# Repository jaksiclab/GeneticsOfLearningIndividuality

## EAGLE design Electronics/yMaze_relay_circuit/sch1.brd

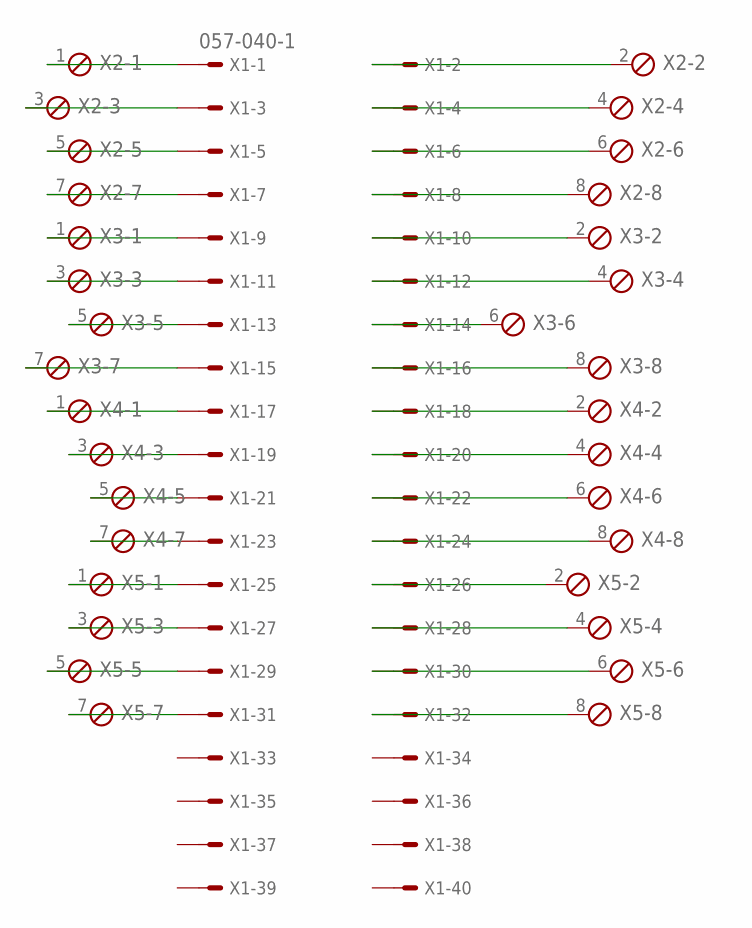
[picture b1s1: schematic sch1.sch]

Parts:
X1: 057-040-1
X2, X3, X4, X5: MPT8; 8POL254

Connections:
unnamed: X1.1, X2.1
unnamed: X1.2, X2.2
unnamed: X1.3, X2.3
unnamed: X1.4, X2.4
unnamed: X1.5, X2.5
unnamed: X1.6, X2.6
unnamed: X1.7, X2.7
unnamed: X1.8, X2.8
unnamed: X1.9, X3.1
unnamed: X1.10, X3.2
unnamed: X1.11, X3.3
unnamed: X1.12, X3.4
unnamed: X1.13, X3.5
unnamed: X1.14, X3.6
unnamed: X1.15, X3.7
unnamed: X1.16, X3.8
unnamed: X1.17, X4.1
unnamed: X1.18, X4.2
unnamed: X1.19, X4.3
unnamed: X1.20, X4.4
unnamed: X1.21, X4.5
unnamed: X1.22, X4.6
unnamed: X1.23, X4.7
unnamed: X1.24, X4.8
unnamed: X1.25, X5.1
unnamed: X1.26, X5.2
unnamed: X1.27, X5.3
unnamed: X1.28, X5.4
unnamed: X1.29, X5.5
unnamed: X1.30, X5.6
unnamed: X1.31, X5.7
unnamed: X1.32, X5.8

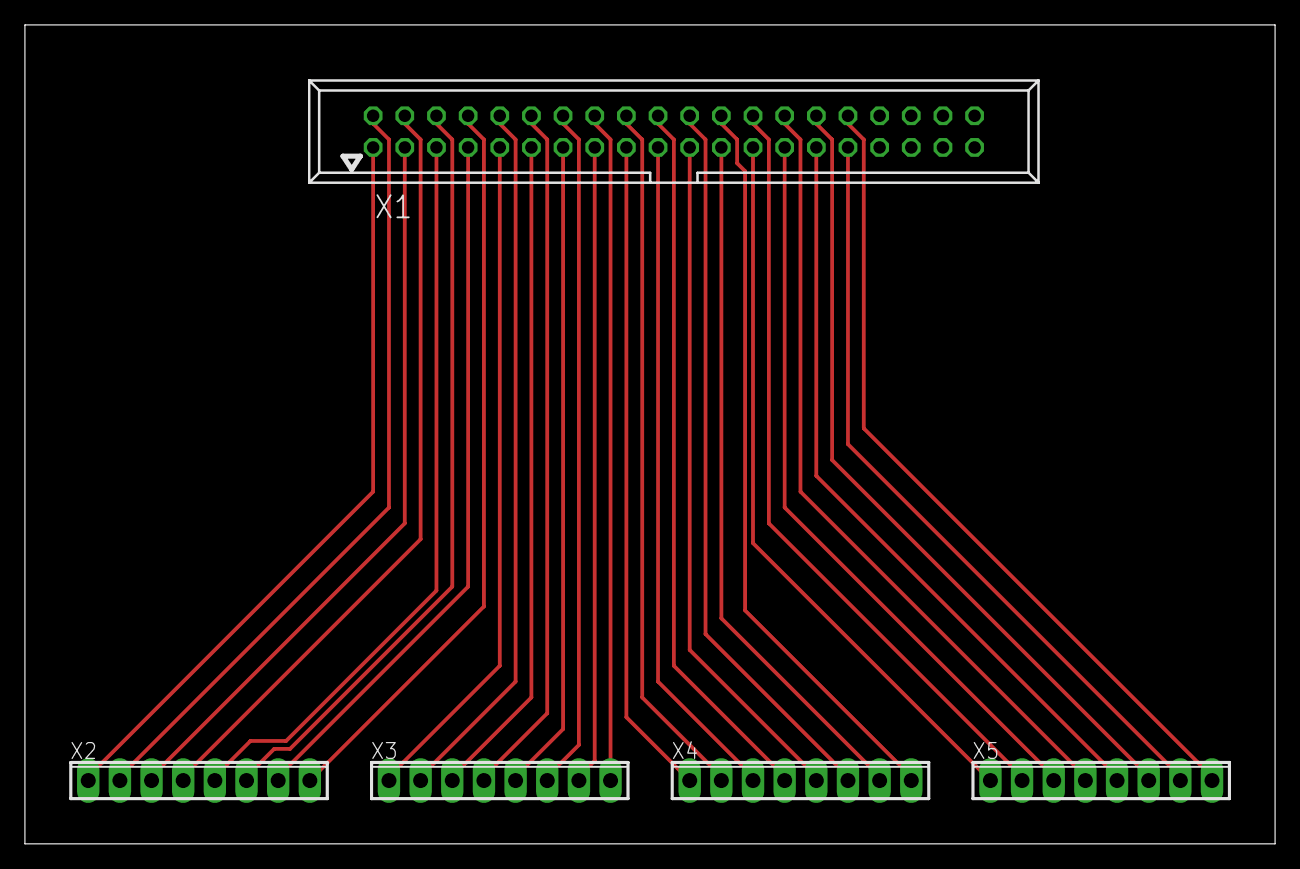
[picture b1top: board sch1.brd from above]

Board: 2 copper layers, 100.3 x 65.7 mm, 5 parts (0 on the bottom side), 32 nets.

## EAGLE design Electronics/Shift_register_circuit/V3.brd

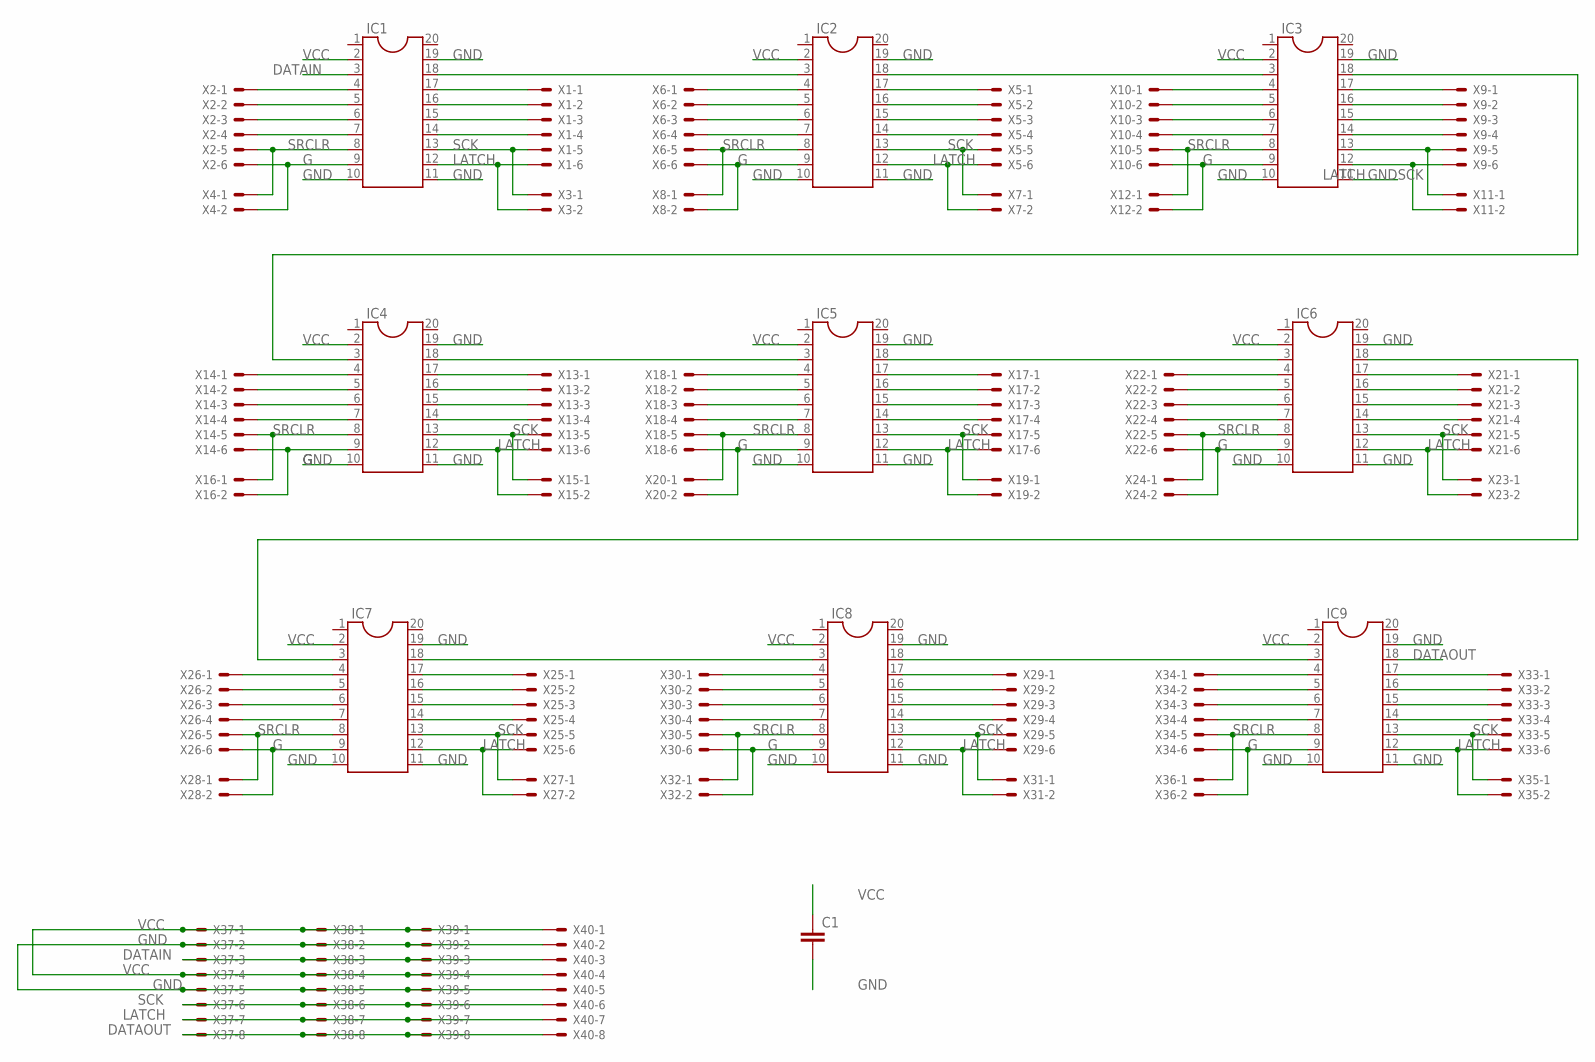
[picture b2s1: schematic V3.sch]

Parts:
C1: C2.5/2; C2.5-2
IC1, IC2, IC3, IC4, IC5, IC6, IC7, IC8, IC9: DIL20
X1, X2, X5, X6, X9, X10, X13, X14, X17, X18, X21, X22, X25, X26, X29, X30, X33, X34: 22-23-2061
X3, X4, X7, X8, X11, X12, X15, X16, X19, X20, X23, X24, X27, X28, X31, X32, X35, X36: 22-23-2021
X37, X38, X39, X40: 22-23-2081

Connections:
DATAIN: IC1.3, X37.3, X38.3, X39.3, X40.3
DATAOUT: IC9.18, X37.8, X38.8, X39.8, X40.8
G: IC1.9, IC2.9, IC3.9, IC4.9, IC5.9, IC6.9, IC7.9, IC8.9, IC9.9, X2.6, X4.2, X6.6, X8.2, X10.6, X12.2, X14.6, X16.2, X18.6, X20.2, X22.6, X24.2, X26.6, X28.2, X30.6, X32.2, X34.6, X36.2
GND: C1.2, IC1.10, IC1.11, IC1.19, IC2.10, IC2.11, IC2.19, IC3.10, IC3.11, IC3.19, IC4.10, IC4.11, IC4.19, IC5.10, IC5.11, IC5.19, IC6.10, IC6.11, IC6.19, IC7.10, IC7.11, IC7.19, IC8.10, IC8.11, IC8.19, IC9.10, IC9.11, IC9.19, X37.2, X37.5, X38.2, X38.5, X39.2, X39.5, X40.2, X40.5
LATCH: IC1.12, IC2.12, IC3.12, IC4.12, IC5.12, IC6.12, IC7.12, IC8.12, IC9.12, X1.6, X3.2, X5.6, X7.2, X9.6, X11.2, X13.6, X15.2, X17.6, X19.2, X21.6, X23.2, X25.6, X27.2, X29.6, X31.2, X33.6, X35.2, X37.7, X38.7, X39.7, X40.7
unnamed: IC1.17, X1.1
unnamed: IC1.16, X1.2
unnamed: IC1.15, X1.3
unnamed: IC1.14, X1.4
unnamed: IC1.4, X2.1
unnamed: IC1.5, X2.2
unnamed: IC1.6, X2.3
unnamed: IC1.7, X2.4
unnamed: IC2.17, X5.1
unnamed: IC2.16, X5.2
unnamed: IC2.15, X5.3
unnamed: IC2.14, X5.4
unnamed: IC2.4, X6.1
unnamed: IC2.5, X6.2
unnamed: IC2.6, X6.3
unnamed: IC2.7, X6.4
unnamed: IC3.17, X9.1
unnamed: IC3.16, X9.2
unnamed: IC3.15, X9.3
unnamed: IC3.14, X9.4
unnamed: IC3.4, X10.1
unnamed: IC3.5, X10.2
unnamed: IC3.6, X10.3
unnamed: IC3.7, X10.4
unnamed: IC4.17, X13.1
unnamed: IC4.16, X13.2
unnamed: IC4.15, X13.3
unnamed: IC4.14, X13.4
unnamed: IC4.4, X14.1
unnamed: IC4.5, X14.2
unnamed: IC4.6, X14.3
unnamed: IC4.7, X14.4
unnamed: IC5.17, X17.1
unnamed: IC5.16, X17.2
unnamed: IC5.15, X17.3
unnamed: IC5.14, X17.4
unnamed: IC5.4, X18.1
unnamed: IC5.5, X18.2
unnamed: IC5.6, X18.3
unnamed: IC5.7, X18.4
unnamed: IC6.17, X21.1
unnamed: IC6.16, X21.2
unnamed: IC6.15, X21.3
unnamed: IC6.14, X21.4
unnamed: IC6.4, X22.1
unnamed: IC6.5, X22.2
unnamed: IC6.6, X22.3
unnamed: IC6.7, X22.4
unnamed: IC7.17, X25.1
unnamed: IC7.16, X25.2
unnamed: IC7.15, X25.3
unnamed: IC7.14, X25.4
unnamed: IC7.4, X26.1
unnamed: IC7.5, X26.2
unnamed: IC7.6, X26.3
unnamed: IC7.7, X26.4
unnamed: IC8.17, X29.1
unnamed: IC8.16, X29.2
unnamed: IC8.15, X29.3
unnamed: IC8.14, X29.4
unnamed: IC8.4, X30.1
unnamed: IC8.5, X30.2
unnamed: IC8.6, X30.3
unnamed: IC8.7, X30.4
unnamed: IC9.17, X33.1
unnamed: IC9.16, X33.2
unnamed: IC9.15, X33.3
unnamed: IC9.14, X33.4
unnamed: IC9.4, X34.1
unnamed: IC9.5, X34.2
unnamed: IC9.6, X34.3
unnamed: IC9.7, X34.4
unnamed: IC1.18, IC2.3
unnamed: IC2.18, IC3.3
unnamed: IC3.18, IC4.3
unnamed: IC4.18, IC5.3
unnamed: IC5.18, IC6.3
unnamed: IC6.18, IC7.3
unnamed: IC7.18, IC8.3
unnamed: IC8.18, IC9.3
SCK: IC1.13, IC2.13, IC3.13, IC4.13, IC5.13, IC6.13, IC7.13, IC8.13, IC9.13, X1.5, X3.1, X5.5, X7.1, X9.5, X11.1, X13.5, X15.1, X17.5, X19.1, X21.5, X23.1, X25.5, X27.1, X29.5, X31.1, X33.5, X35.1, X37.6, X38.6, X39.6, X40.6
SRCLR: IC1.8, IC2.8, IC3.8, IC4.8, IC5.8, IC6.8, IC7.8, IC8.8, IC9.8, X2.5, X4.1, X6.5, X8.1, X10.5, X12.1, X14.5, X16.1, X18.5, X20.1, X22.5, X24.1, X26.5, X28.1, X30.5, X32.1, X34.5, X36.1
VCC: C1.1, IC1.2, IC2.2, IC3.2, IC4.2, IC5.2, IC6.2, IC7.2, IC8.2, IC9.2, X37.1, X37.4, X38.1, X38.4, X39.1, X39.4, X40.1, X40.4

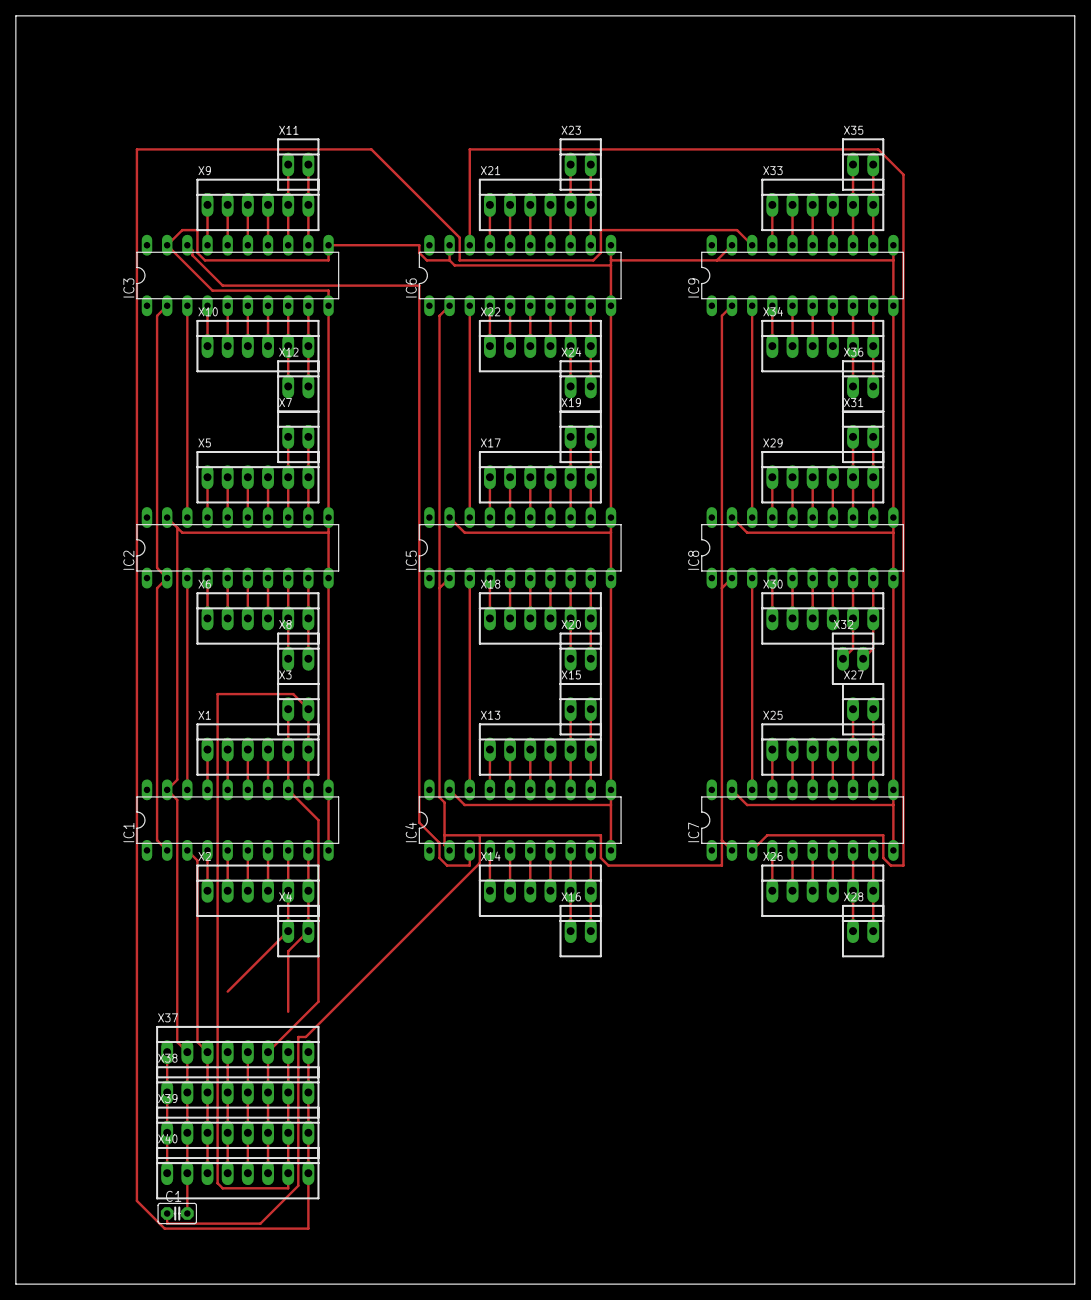
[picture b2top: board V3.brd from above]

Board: 2 copper layers, 133.3 x 159.7 mm, 50 parts (0 on the bottom side), 88 nets.

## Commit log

2024-04-28 first push
2024-04-30 added repeated measures data
2024-07-29 purge
2024-07-29 adding data and code before submission
2024-11-04 push
2024-11-05 push again
2024-12-12 adding simulation codes and data
2025-08-19 Update LICENSE
